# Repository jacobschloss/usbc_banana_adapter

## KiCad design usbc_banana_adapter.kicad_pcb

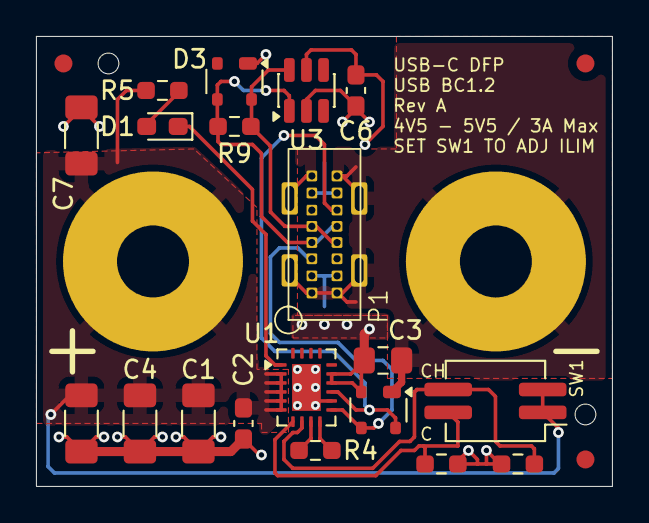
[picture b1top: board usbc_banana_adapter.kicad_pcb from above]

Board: 2 copper layers, 32.0 x 25.0 mm, 26 parts (0 on the bottom side), 13 nets.

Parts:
C1, C4, C5, C7: 47uF; C_1206_3216Metric_Pad1.33x1.80mm_HandSolder
C2, C6: 100nF; C_0603_1608Metric_Pad1.08x0.95mm_HandSolder
C3: 10uF; C_0805_2012Metric_Pad1.18x1.45mm_HandSolder
D1: KT-0603R; LED_0603_1608Metric_Pad1.05x0.95mm_HandSolder
D3, D4: SP0503BAHTG; SOT-143
FID1, FID2, FID3: Fiducial; Fiducial_1mm_Mask2mm
H1, H2: MountingHole_Pad; MountingHole_4mmx10mm_#6_loose
H5, H6: MountingHole; ToolingHole_1.152mm
P1: UJ20-C-V-C-3-SMT-TR
R4, R7, R8: 100k; R_0603_1608Metric_Pad0.98x0.95mm_HandSolder
R5: 10k; R_0603_1608Metric_Pad0.98x0.95mm_HandSolder
R9: 0; R_0603_1608Metric_Pad0.98x0.95mm_HandSolder
SW1: DSHP02TJGER; SW_DIP_SPSTx02_Slide_KingTek_DSHP02TJ_W5.25mm_P1.27mm_JPin
U1: TPS25810RVCR; Texas_RVC0020A_WQFN-20-1EP_3x4mm_P0.5mm_EP1.6x2.6mm
U3: TPS2514DBVR; SOT-23-6

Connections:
+5V: C1.1, C2.1, C4.1, C5.1, C7.1, H1.1 (1_1), R5.1, SW1.1, SW1.2, U1.2 (IN1), U1.3 (IN1), U1.4 (IN2), U1.5 (AUX), U1.6 (EN)
/VBUS: C3.1, C6.1, D4.2 (K), P1.A4 (VBUS), P1.A9 (VBUS), P1.B4 (VBUS), P1.B9 (VBUS), U1.14 (OUT), U1.15 (OUT), U3.5 (IN)
GND: C1.2, C2.2, C3.2, C4.2, C5.2, C6.2, C7.2, D3.1 (A), D4.1 (A), H2.1 (1_1), P1.A1 (GND), P1.A12 (GND), P1.B1 (GND), P1.B12 (GND), P1.SH (SHIELD), R7.2, R8.2, U1.12 (GND), U1.21 (GND), U3.2 (GND)
unnamed: D1.2 (A), R5.2
unnamed: D1.1 (K), U1.1 (~FAULT)
unnamed: D4.3 (K), P1.A5 (CC1), U1.11 (CC1)
unnamed: D4.4 (K), P1.B5 (CC2), U1.13 (CC2)
unnamed: R8.1, SW1.4, U1.7 (CHG)
unnamed: R7.1, SW1.3, U1.8 (CHG_HI)
unnamed: R4.1, U1.10 (REF)
unnamed: R4.2, U1.9 (REF_RTN)
unnamed: D3.4 (K), P1.A7 (D-), P1.B7 (D-), R9.1, U3.6 (DM1)
unnamed: D3.3 (K), P1.A6 (D+), P1.B6 (D+), R9.2, U3.1 (DP1)

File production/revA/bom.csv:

Designator,Footprint,Quantity,Value,LCSC Part #
"C1, C4, C5, C7",1206,4,47uF,C96123
"C2, C6",0603,2,100nF,C14663
C3,0805,1,10uF,C440198
D1,0603,1,KT-0603R,C2286
"D3, D4",SOT-143,2,SP0503BAHTG,C7074
P1,UJ20-C-V-C-3-SMT-TR,1,UJ20-C-V-C-3-SMT-TR,C32689525
"R4, R7, R8",0603,3,100k,C25803
R5,0603,1,10k,C25804
R9,0603,1,0,C21189
SW1,SW_DIP_SPSTx02_Slide_KingTek_DSHP02TJ_W5.25mm_P1.27mm_JPin,1,DSHP02TJGER,C5301819
U1,Texas_RVC0020A_WQFN-20-1EP_3x4mm_P0.5mm_EP1.6x2.6mm,1,TPS25810RVCR,C473913
U3,SOT-23-6,1,TPS2514DBVR,C49754

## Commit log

2026-06-02 init
2026-06-04 active proto negotiation
2026-06-04 layout
2026-06-04 revA ready
2026-06-05 swap banana
2026-06-05 tweak via size
2026-06-08 add diode
